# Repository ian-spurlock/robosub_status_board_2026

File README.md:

# robosub_status_board_2026
kicad files and code for status board

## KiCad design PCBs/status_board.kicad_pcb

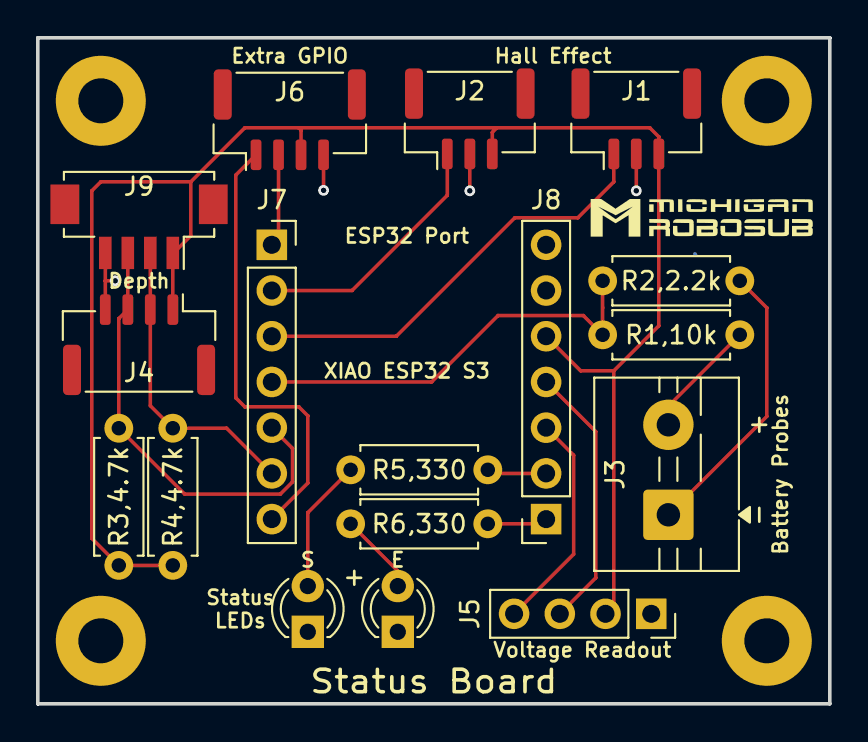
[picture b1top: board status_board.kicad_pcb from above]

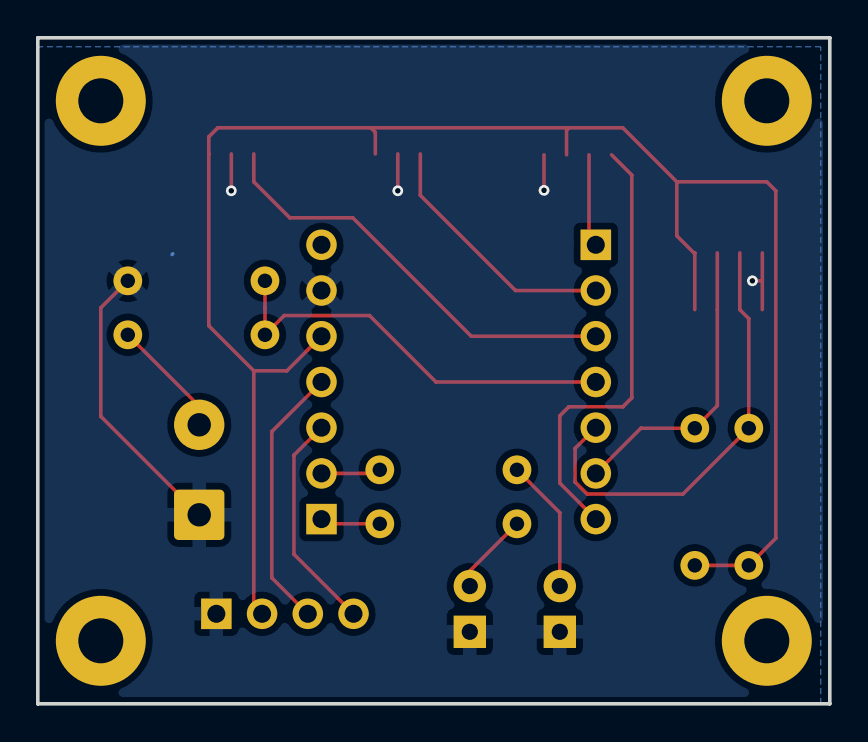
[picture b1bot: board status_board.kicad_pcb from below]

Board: 2 copper layers, 44.0 x 37.0 mm, 22 parts (4 on the bottom side), 16 nets.

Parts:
 : LOGO
D1, D2: LED; LED_D3.0mm
H1, H2, H3, H4: MountingHole; MountingHole_2.5mm_Pad
J1, J2: Conn_01x03; JST_GH_BM03B-GHS-TBT_1x03-1MP_P1.25mm_Vertical
J3: Conn_01x02; TerminalBlock_MaiXu_MX126-5.0-02P_1x02_P5.00mm
J4, J6: Conn_01x04; JST_GH_BM04B-GHS-TBT_1x04-1MP_P1.25mm_Vertical
J5: Conn_01x04; PinSocket_1x04_P2.54mm_Vertical
J7, J8: Conn_01x07; PinSocket_1x07_P2.54mm_Vertical
J9: Conn_01x04; Hirose_DF13C_CL535-0404-8-51_1x04-1MP_P1.25mm_Vertical
R1,10k: 10k; R_Axial_DIN0207_L6.3mm_D2.5mm_P7.62mm_Horizontal
R2,2.2k: 2.2k; R_Axial_DIN0207_L6.3mm_D2.5mm_P7.62mm_Horizontal
R3,4.7k, R4,4.7k: 4.7k; R_Axial_DIN0207_L6.3mm_D2.5mm_P7.62mm_Horizontal
R5,330, R6,330: 330; R_Axial_DIN0207_L6.3mm_D2.5mm_P7.62mm_Horizontal

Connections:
GND: D1.1 (K), D2.1 (K), J1.2, J2.2, J3.1, J4.4, J5.1, J6.4, J8.6, J9.4, R2,2.2k.1
unnamed: D1.2 (A), R6,330.1
unnamed: D2.2 (A), R5,330.1
unnamed: J1.1, J7.3
unnamed: J1.3, J2.3, J4.1, J5.2, J6.3, J8.5, J9.1, R3,4.7k.2, R4,4.7k.1
unnamed: J2.1, J7.2
unnamed: J3.2, R1,10k.1
unnamed: J4.2, J7.6, J9.2, R4,4.7k.2
unnamed: J4.3, J7.5, J9.3, R3,4.7k.1
unnamed: J5.3, J8.4
unnamed: J5.4, J8.3
unnamed: J6.1, J7.7
unnamed: J6.2, J7.1
unnamed: J7.4, R1,10k.2, R2,2.2k.2
unnamed: J8.1, R6,330.2
unnamed: J8.2, R5,330.2
